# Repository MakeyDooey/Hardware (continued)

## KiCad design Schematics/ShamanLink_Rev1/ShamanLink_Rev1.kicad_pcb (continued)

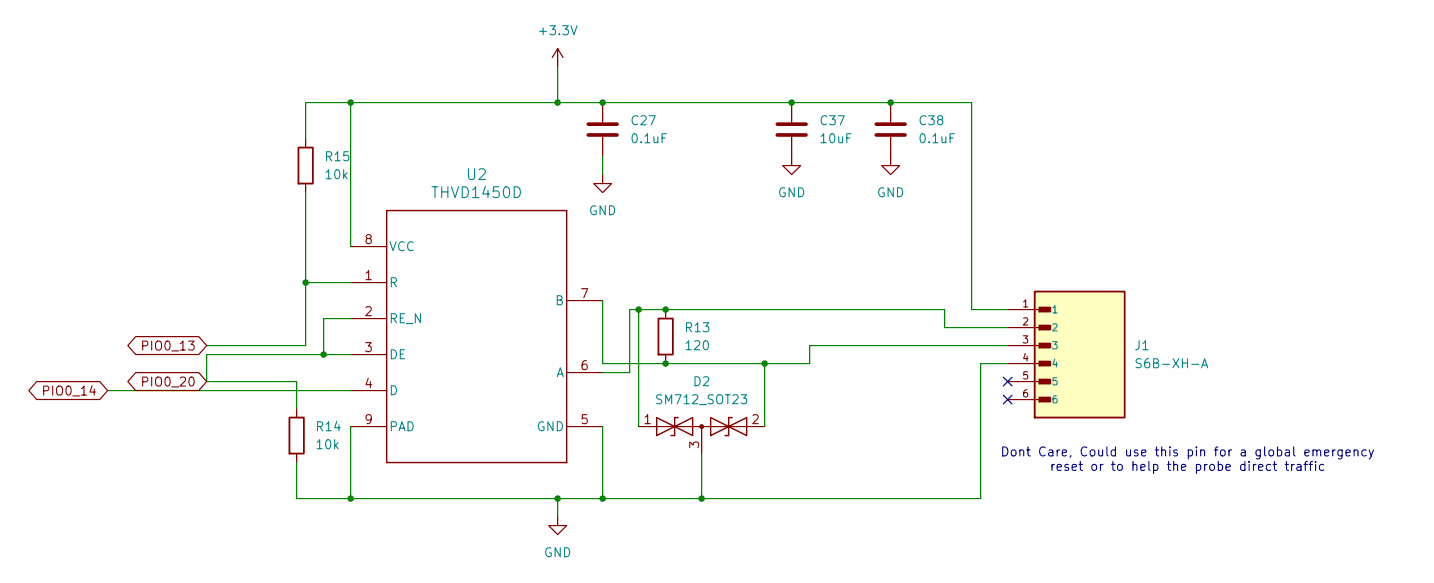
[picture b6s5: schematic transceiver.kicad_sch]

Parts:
C27, C38: 0.1uF; C_0805_2012Metric_Pad1.18x1.45mm_HandSolder
C37: 10uF; C_0805_2012Metric_Pad1.18x1.45mm_HandSolder
D2: SM712_SOT23; SOT-23_Handsoldering
J1: S6B-XH-A; JST_S6B-XH-A
R13: 120; R_1206_3216Metric_Pad1.30x1.75mm_HandSolder
R14, R15: 10k; R_0805_2012Metric_Pad1.20x1.40mm_HandSolder
U2: THVD1450D; D0008A_M

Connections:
+3.3V: C27.1, C37.1, C38.1, J1.1, R15.1, U2.8 (VCC); also elsewhere on the board
GND: C27.2, C37.2, C38.2, D2.3 (common), J1.4, R14.2, U2.5 (GND), U2.9 (PAD); also elsewhere on the board
unnamed: D2.1 (A1), J1.2, R13.1, U2.6 (A)
unnamed: D2.2 (A2), J1.3, R13.2, U2.7 (B)
PIO0_13: R15.2, U2.1 (R); also elsewhere on the board
PIO0_14: U2.4 (D); also elsewhere on the board
PIO0_20: R14.1, U2.2 (RE_N), U2.3 (DE); also elsewhere on the board

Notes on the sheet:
Dont Care, Could use this pin for a global emergency reset or to help the probe direct traffic

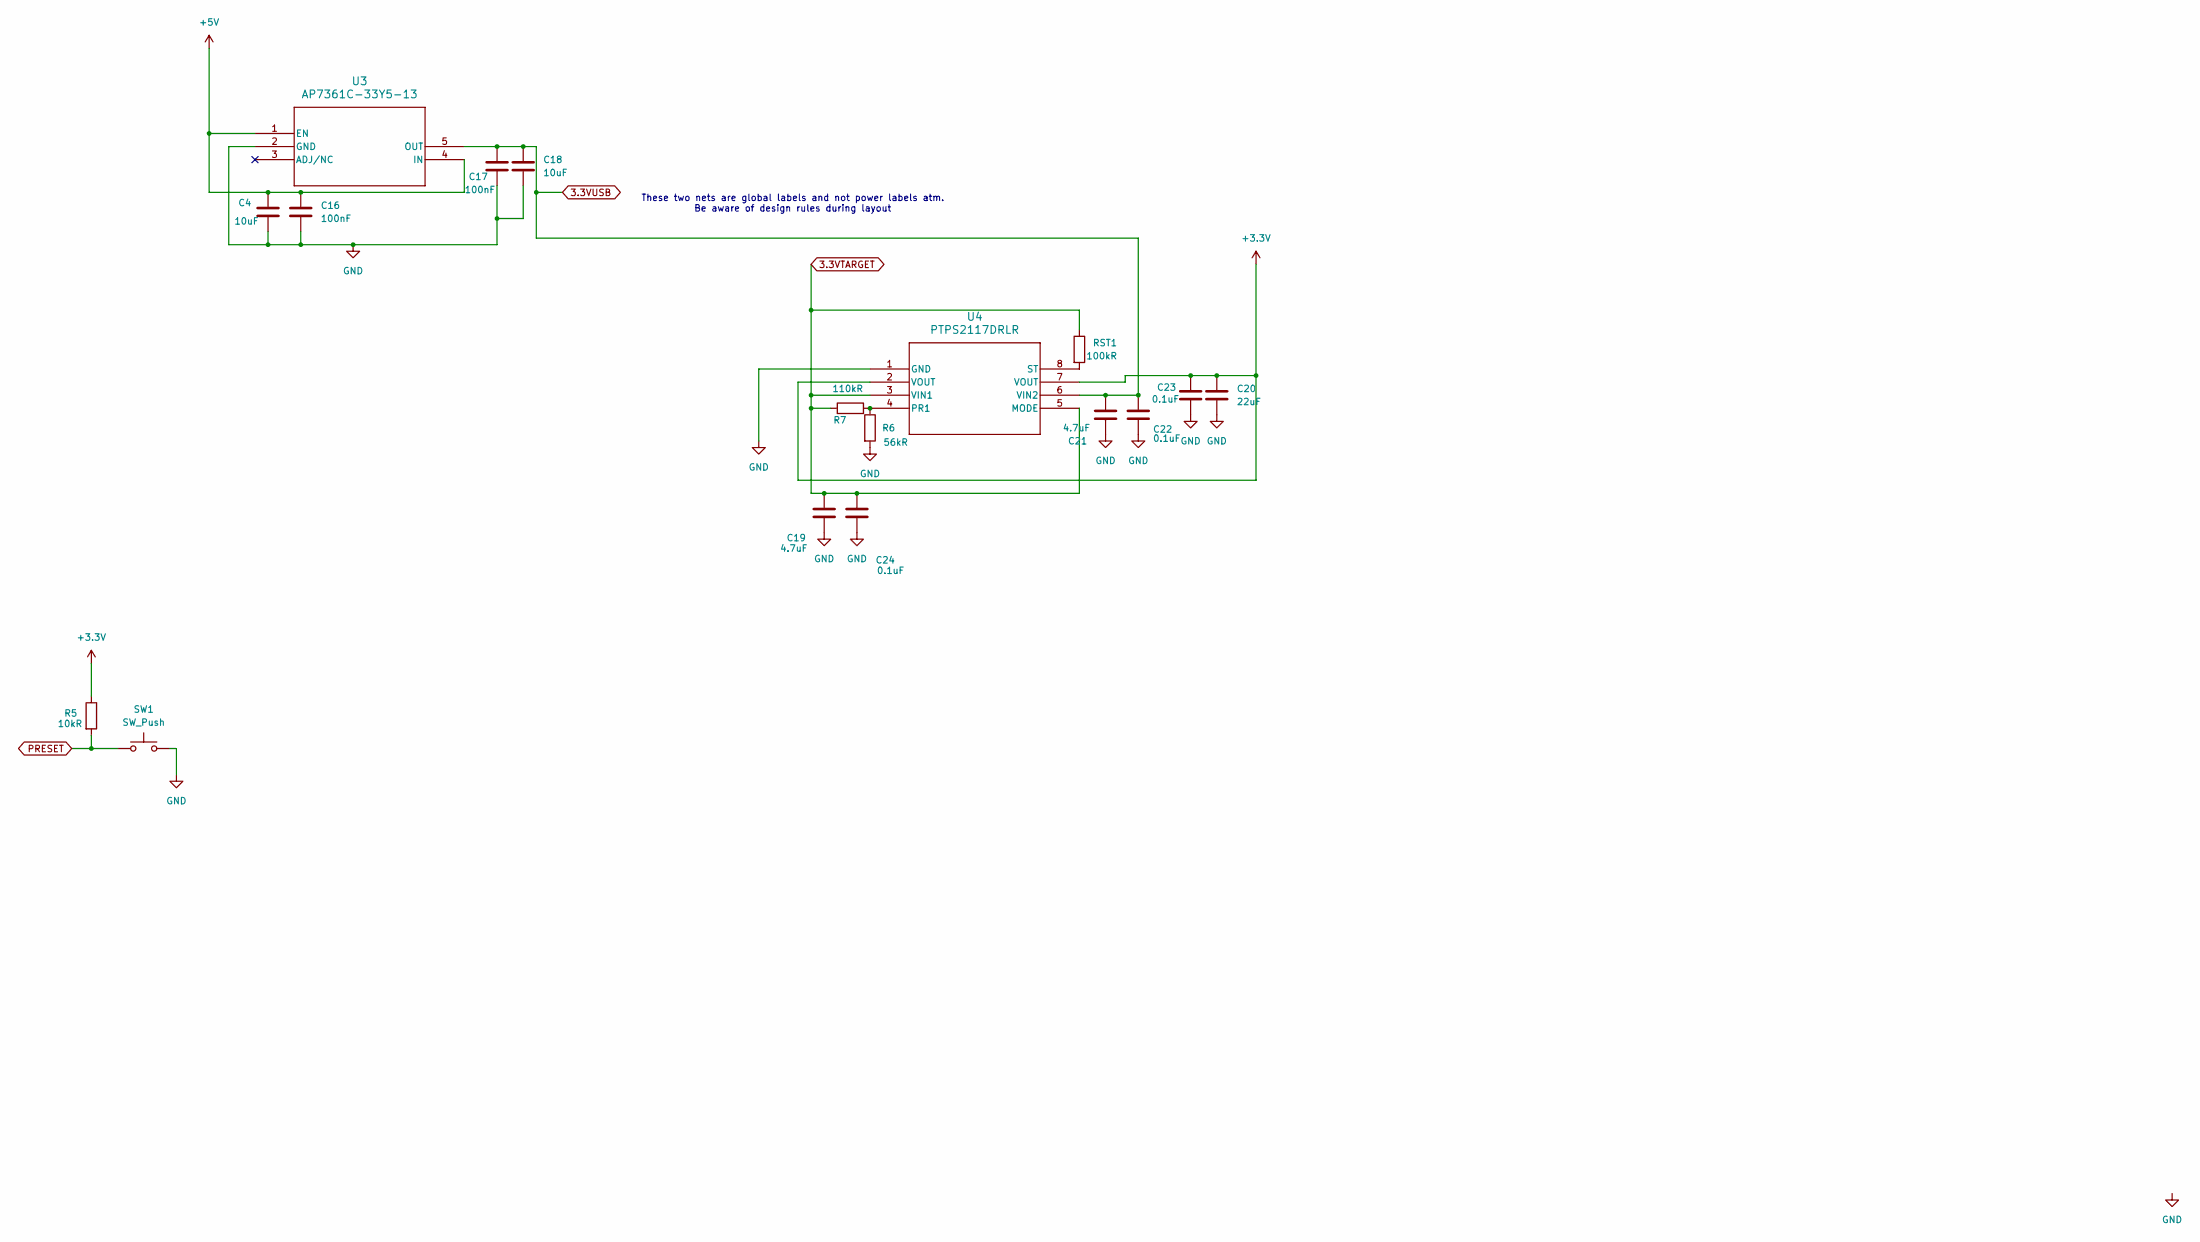
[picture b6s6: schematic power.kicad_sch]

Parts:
C4, C18: 10uF; C_0805_2012Metric_Pad1.18x1.45mm_HandSolder
C16, C17: 100nF; C_0805_2012Metric_Pad1.18x1.45mm_HandSolder
C19, C21: 4.7uF; C_0805_2012Metric_Pad1.18x1.45mm_HandSolder
C20: 22uF; C_1206_3216Metric_Pad1.33x1.80mm_HandSolder
C22, C23, C24: 0.1uF; C_0805_2012Metric_Pad1.18x1.45mm_HandSolder
R5: 10kR; R_0805_2012Metric_Pad1.20x1.40mm_HandSolder
R6: 56kR; R_0805_2012Metric_Pad1.20x1.40mm_HandSolder
R7: 110kR; R_0805_2012Metric_Pad1.20x1.40mm_HandSolder
RST1: 100kR; R_0805_2012Metric_Pad1.20x1.40mm_HandSolder
SW1: SW_Push; SW_SPST_PTS645Sx43SMTR92
U3: AP7361C-33Y5-13; SOT89-5_DIO
U4: PTPS2117DRLR; SOT-5X3-8_DRL_TEX-M

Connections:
3.3VTARGET: C19.1, C24.1, R7.1, RST1.1, U4.3 (VIN1), U4.5 (MODE); also elsewhere on the board
3.3VUSB: C17.1, C18.1, C21.1, C22.1, U3.5 (OUT), U4.6 (VIN2); also elsewhere on the board
+3.3V: C20.1, C23.1, R5.1, U4.2 (VOUT), U4.7 (VOUT); also elsewhere on the board
+5V: C4.1, C16.1, U3.1 (EN), U3.4 (IN); also elsewhere on the board
GND: C4.2, C16.2, C17.2, C18.2, C19.2, C20.2, C21.2, C22.2, C23.2, C24.2, R6.2, SW1.2, U3.2 (GND), U4.1 (GND); also elsewhere on the board
unnamed: R6.1, R7.2, U4.4 (PR1)
unnamed: RST1.2, U4.8 (ST)
PRESET: R5.2, SW1.1; also elsewhere on the board

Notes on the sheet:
These two nets are global labels and not power labels atm. Be aware of design rules during layout

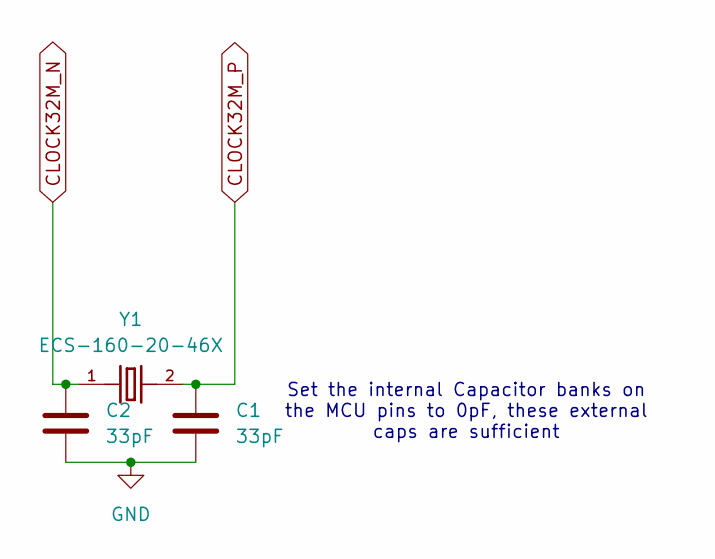
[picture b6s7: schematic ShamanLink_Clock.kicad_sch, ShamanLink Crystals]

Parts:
C1, C2: 33pF; C_0805_2012Metric_Pad1.18x1.45mm_HandSolder
Y1: ECS-160-20-46X; XTAL_ECS-160-20-46X

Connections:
CLOCK32M_N: C2.1, Y1.1; also elsewhere on the board
CLOCK32M_P: C1.1, Y1.2; also elsewhere on the board
GND: C1.2, C2.2; also elsewhere on the board

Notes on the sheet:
Set the internal Capacitor banks on the MCU pins to 0pF, these external caps are sufficient

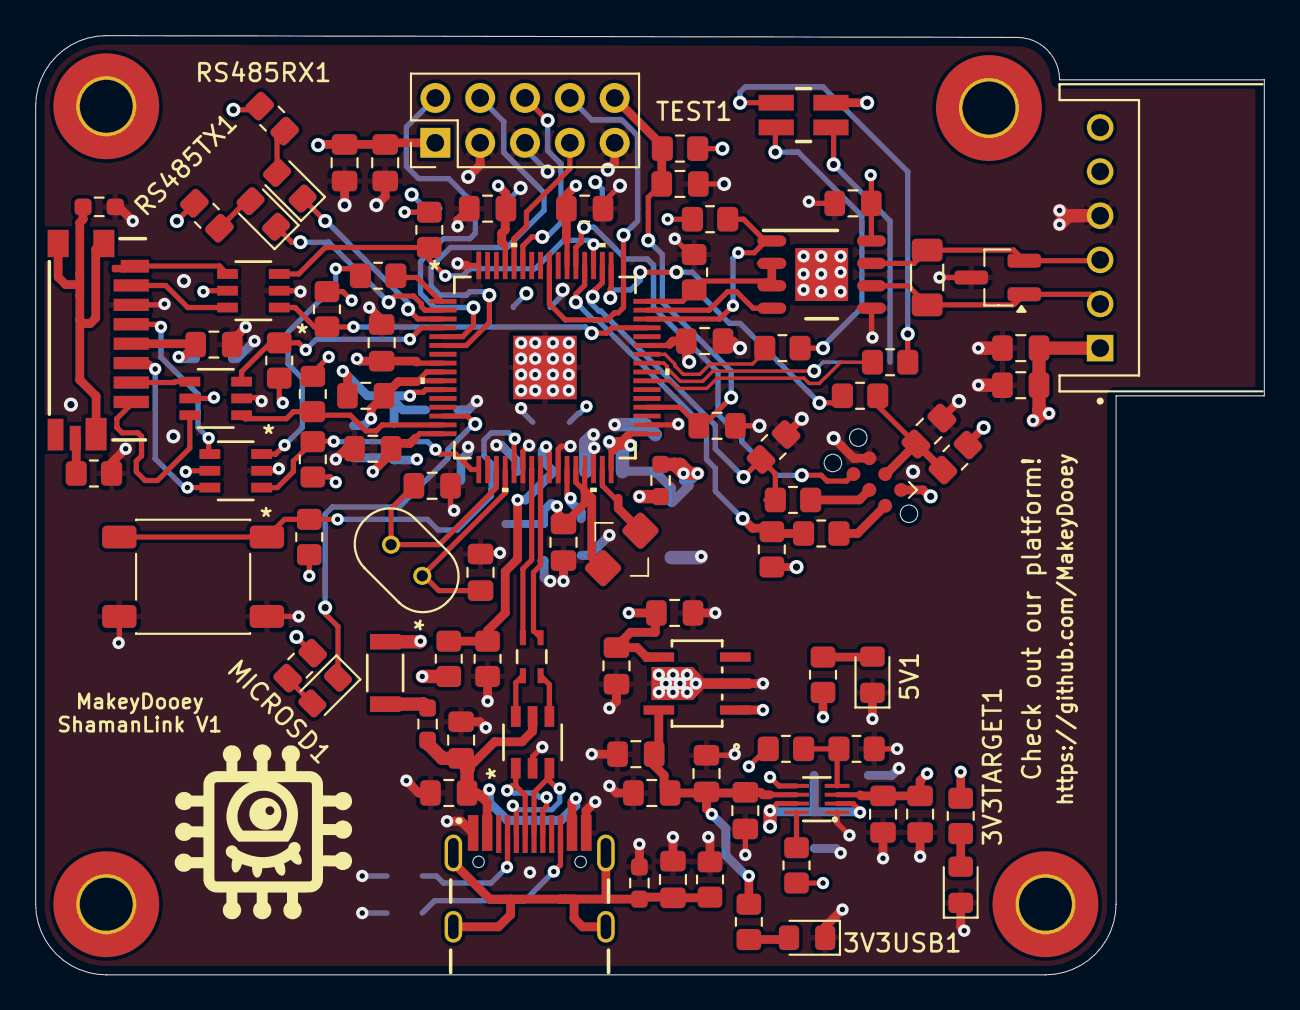
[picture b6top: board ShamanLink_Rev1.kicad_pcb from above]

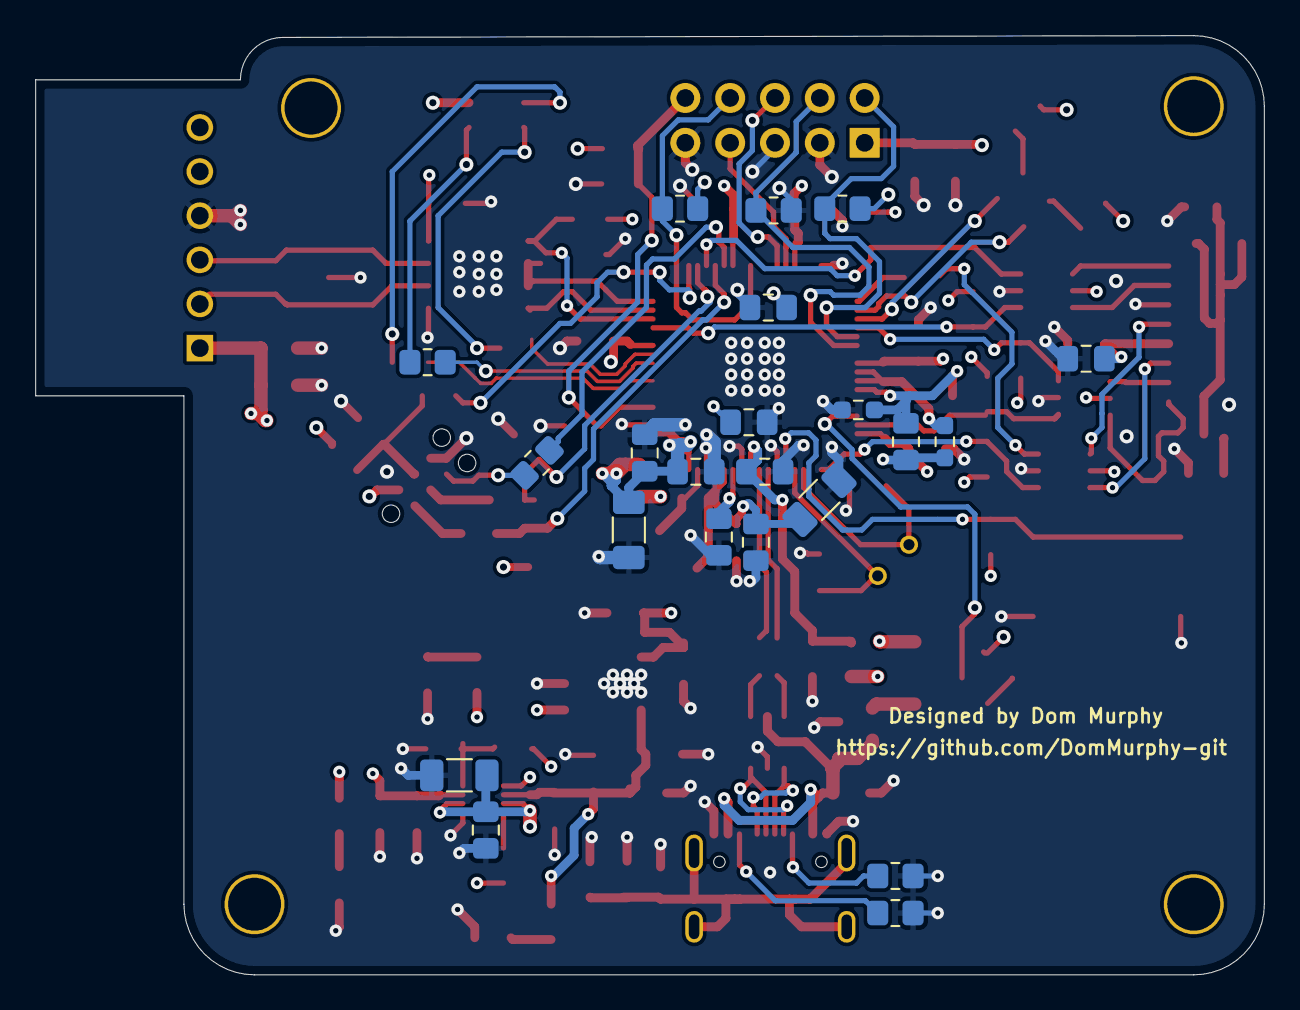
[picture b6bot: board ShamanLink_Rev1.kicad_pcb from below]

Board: 4 copper layers, 69.6 x 53.2 mm, 117 parts (22 on the bottom side), 76 nets.

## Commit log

2025-11-05 Add Python Script for USB Testing
2025-11-06 Add Component Testing - Dominic Murphy
2026-02-24 Finished the ShamanLink PCB Design
2026-02-24 Clarified SWO UART tradeoff implemenation
2026-03-28 Add initial README for CAD files
2026-04-02 Final ShamanLink Revisions and Motor Totem Final Revisions
2026-04-02 Added RS485 functionality to MainTotemLite
2026-04-07 Adding the MTL Schematics in post editing
2026-04-08 Layout Edits for Mezzanine Connector routing
2026-04-08 Rerouting layout to resolve collision issues
2026-04-08 Adding Gerber and CAD files
2026-04-11 Computer Vision Module Alterations
2026-04-11 Added Bottom Module GPIO Demo board
2026-04-26 CAD files and Schematic PDFs
